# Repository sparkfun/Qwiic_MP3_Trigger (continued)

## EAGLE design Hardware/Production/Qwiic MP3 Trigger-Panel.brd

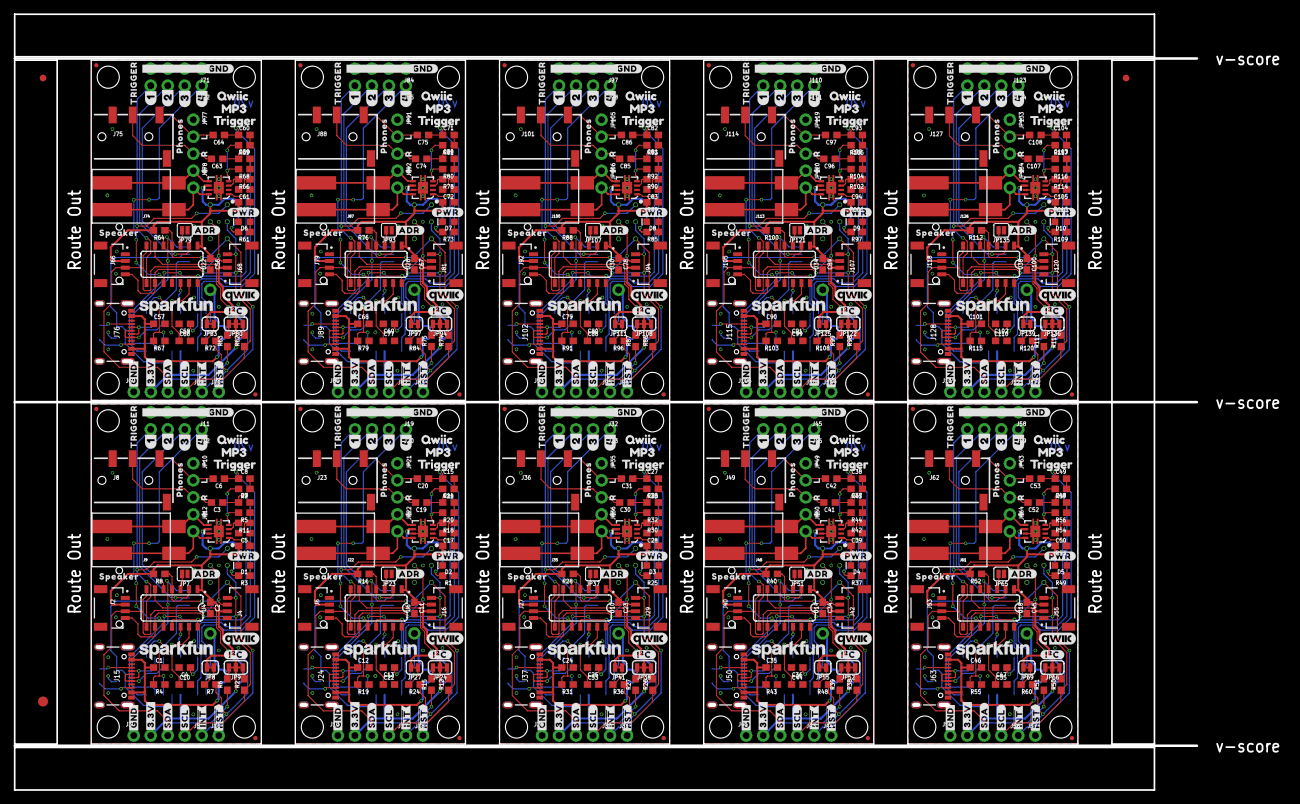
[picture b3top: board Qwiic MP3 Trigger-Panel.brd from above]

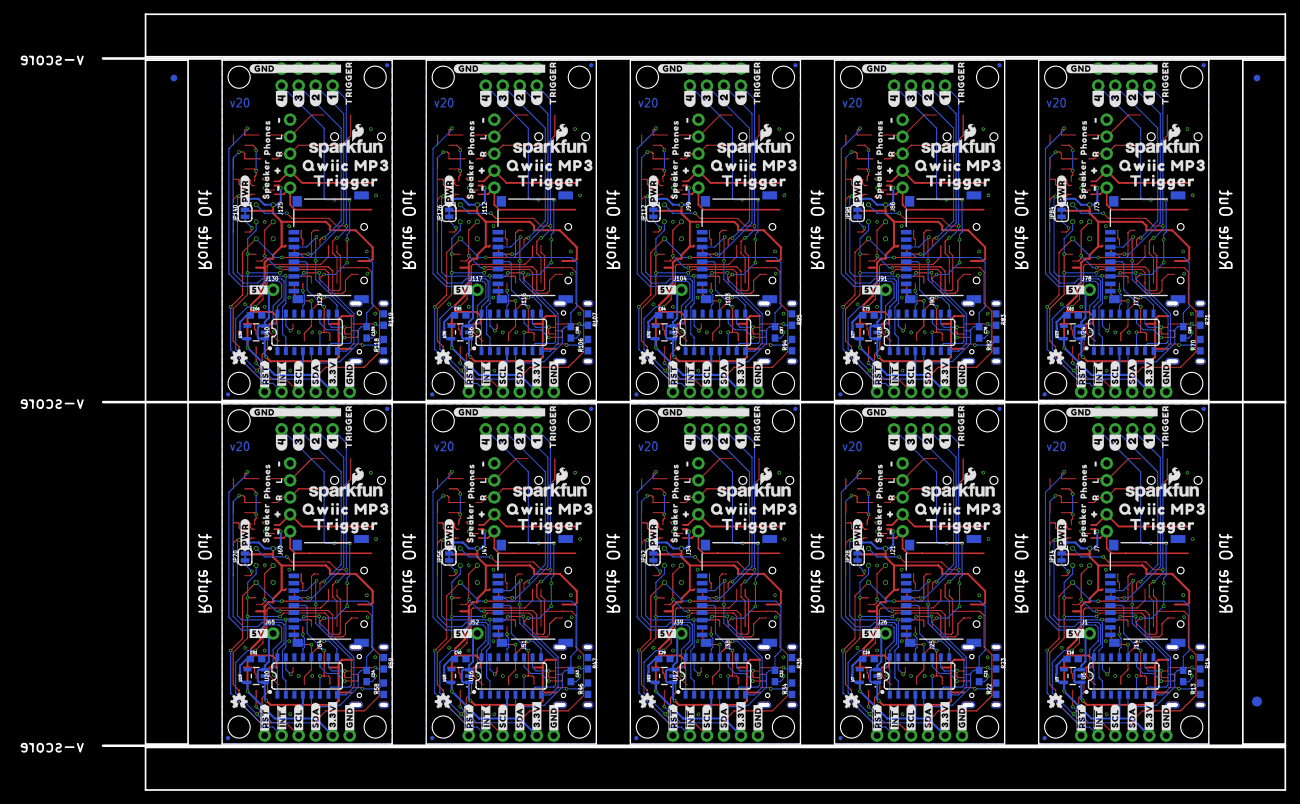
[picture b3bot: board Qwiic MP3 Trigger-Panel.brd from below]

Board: 2 copper layers, 176.5 x 115.8 mm, 1076 parts (373 on the bottom side), 410 nets.

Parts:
C1, C9, C12, C16, C18, C21, C24, C29, C32, C35, C40, C43, C46, C51, C54, C57, C62, C65, C68, C73, C76, C79, C84, C87, C90, C95, C98, C101, C106, C109: 1.0uF; 0603
C2, C11, C23, C34, C45, C56, C67, C78, C89, C100: 0.1uF; 0603
C3, C6, C19, C20, C30, C31, C41, C42, C52, C53, C63, C64, C74, C75, C85, C86, C96, C97, C107, C108: 0.22uF; 0603
C4, C10, C13, C22, C25, C33, C36, C44, C47, C55, C58, C66, C69, C77, C80, C88, C91, C99, C102, C110: 2.2uF; 0603
C5, C17, C28, C39, C50, C61, C72, C83, C94, C105: 22nF; 0603
C7, C8, C14, C15, C26, C27, C37, C38, C48, C49, C59, C60, C70, C71, C81, C82, C92, C93, C103, C104: 10nF; 0603
D1, D2, D3, D4, D5, D6, D7, D8, D9, D10: RED; LED-0603
E$1, E$2, E$3, E$4: FIDUCIAL-1X2
E$5, E$6: FIDUCIAL-1.5X3
J1, J5, J10, J17, J18, J26, J30, J31, J39, J43, J44, J52, J56, J57, J65, J69, J70, J78, J82, J83, J91, J95, J96, J104, J108, J109, J117, J121, J122, J130: 1X01_NO_SILK
J2, J4, J6, J16, J27, J29, J40, J42, J53, J55, J66, J68, J79, J81, J92, J94, J105, J107, J118, J120: QWIIC_RIGHT_ANGLE; JST04_1MM_RA
J3, J13, J28, J41, J54, J67, J80, J93, J106, J119: PTH; 1X04_NO_SILK
J7, J21, J34, J47, J60, J73, J86, J99, J112, J125: ISP; 2X3_TEST_POINTS
J8, J23, J36, J49, J62, J75, J88, J101, J114, J127: 3.5mm Audio; AUDIO_JACK_3.5MM_TRRS_SMD_RA
J9, J22, J35, J48, J61, J74, J87, J100, J113, J126: Poke-Home; 1X02_POKEHOME
J11, J12, J19, J20, J32, J33, J45, J46, J58, J59, J71, J72, J84, J85, J97, J98, J110, J111, J123, J124: 1X04_NO_SILK
J14, J25, J38, J51, J64, J77, J90, J103, J116, J129: MICRO-SD; MICROSD-EXTERNALPIN
J15, J24, J37, J50, J63, J76, J89, J102, J115, J128: USB-C-16P-2LAYER-PADS
JP1, JP2, JP5, JP6, JP17, JP18, JP19, JP20, JP31, JP32, JP33, JP34, JP45, JP46, JP47, JP48, JP59, JP60, JP61, JP62, JP73, JP74, JP75, JP76, JP87, JP88, JP89, JP90, JP101, JP102, JP103, JP104, JP115, JP116, JP117, JP118, JP129, JP130, JP131, JP132: FIDUCIALUFIDUCIAL; MICRO-FIDUCIAL
JP3, JP4, JP11, JP13, JP15, JP16, JP25, JP26, JP29, JP30, JP39, JP40, JP43, JP44, JP53, JP54, JP57, JP58, JP67, JP68, JP71, JP72, JP81, JP82, JP85, JP86, JP95, JP96, JP99, JP100, JP109, JP110, JP113, JP114, JP123, JP124, JP127, JP128, JP137, JP138: STAND-OFF
JP7, JP23, JP37, JP51, JP65, JP79, JP93, JP107, JP121, JP135: ADR; SMT-JUMPER_2_NO_SILK
JP8, JP27, JP41, JP55, JP69, JP83, JP97, JP111, JP125, JP139: INT; SMT-JUMPER_2_NC_TRACE_SILK
JP9, JP24, JP38, JP52, JP66, JP80, JP94, JP108, JP122, JP136: JUMPER-SMT_3_2-NC_TRACE_SILK; SMT-JUMPER_3_2-NC_TRACE_SILK
JP10, JP21, JP35, JP49, JP63, JP77, JP91, JP105, JP119, JP133: PTH; 1X03_NO_SILK
JP12, JP22, JP36, JP50, JP64, JP78, JP92, JP106, JP120, JP134: PTH; 1X02_NO_SILK
JP14, JP28, JP42, JP56, JP70, JP84, JP98, JP112, JP126, JP140: JUMPER-SMT_2_NC_TRACE_SILK; SMT-JUMPER_2_NC_TRACE_SILK
LOGO1, LOGO5, LOGO9, LOGO13, LOGO17, LOGO21, LOGO25, LOGO29, LOGO33, LOGO37: OSHW-LOGOMINI; OSHW-LOGO-MINI
LOGO2, LOGO6, LOGO10, LOGO14, LOGO18, LOGO22, LOGO26, LOGO30, LOGO34, LOGO38: SFE_LOGO_NAME.1_INCH; SFE_LOGO_NAME_.1
LOGO3, LOGO7, LOGO11, LOGO15, LOGO19, LOGO23, LOGO27, LOGO31, LOGO35, LOGO39: SFE_LOGO_NAME_FLAME.1_INCH; SFE_LOGO_NAME_FLAME_.1
LOGO4, LOGO8, LOGO12, LOGO16, LOGO20, LOGO24, LOGO28, LOGO32, LOGO36, LOGO40: QWIIC_LOGO_CONNECTOR; QWIIC_5.5MM
R1, R3, R25, R37, R49, R61, R73, R85, R97, R109: 1k; 0603
R2, R4, R6, R12, R15, R19, R26, R27, R31, R38, R39, R43, R50, R51, R55, R62, R63, R67, R74, R75, R79, R86, R87, R91, R98, R99, R103, R110, R111, R115: 2.2k; 0603
R5, R9, R20, R21, R32, R33, R44, R45, R56, R57, R68, R69, R80, R81, R92, R93, R104, R105, R116, R117: 100k; 0603
R7, R8, R10, R16, R17, R24, R28, R29, R36, R40, R41, R48, R52, R53, R60, R64, R65, R72, R76, R77, R84, R88, R89, R96, R100, R101, R108, R112, R113, R120: 10k; 0603
R11, R18, R30, R42, R54, R66, R78, R90, R102, R114: 47k; 0603
R13, R14, R22, R23, R34, R35, R46, R47, R58, R59, R70, R71, R82, R83, R94, R95, R106, R107, R118, R119: 5.1k; 0603
U1, U2, U9, U13, U17, U21, U25, U29, U33, U37: TPA2005D1; QFN-8_PAD
U3, U7, U11, U15, U19, U23, U27, U31, U35, U39: AP2112-3.3V; SOT23-5
U4, U6, U10, U14, U18, U22, U26, U30, U34, U38: ATTINY84-ARDUINO; SO14
U5, U8, U12, U16, U20, U24, U28, U32, U36, U40: MY1690X-16S; SO16
U$1, U$4, U$97, U$145, U$193, U$241, U$289, U$337, U$385, U$433: MP31
U$2, U$27, U$30, U$47, U$109, U$110, U$157, U$158, U$205, U$206, U$253, U$254, U$301, U$302, U$349, U$350, U$397, U$398, U$445, U$446: TRIGGER0
U$3, U$96, U$144, U$192, U$240, U$288, U$336, U$384, U$432, U$480: #5V#0
U$5, U$23, U$98, U$146, U$194, U$242, U$290, U$338, U$386, U$434: QWIIC0
U$6, U$50, U$99, U$147, U$195, U$243, U$291, U$339, U$387, U$435: TRIGGER2
U$7, U$32, U$48, U$79, U$100, U$127, U$148, U$175, U$196, U$223, U$244, U$271, U$292, U$319, U$340, U$367, U$388, U$415, U$436, U$463: PHONES0
U$8, U$18, U$40, U$82, U$101, U$130, U$149, U$178, U$197, U$226, U$245, U$274, U$293, U$322, U$341, U$370, U$389, U$418, U$437, U$466: SPEAKER0
U$9, U$11, U$14, U$51, U$102, U$103, U$150, U$151, U$198, U$199, U$246, U$247, U$294, U$295, U$342, U$343, U$390, U$391, U$438, U$439: #0
U$10, U$38, U$69, U$70, U$117, U$118, U$165, U$166, U$213, U$214, U$261, U$262, U$309, U$310, U$357, U$358, U$405, U$406, U$453, U$454: #1#3
U$12, U$13, U$16, U$28, U$104, U$105, U$152, U$153, U$200, U$201, U$248, U$249, U$296, U$297, U$344, U$345, U$392, U$393, U$440, U$441: #1
U$15, U$24, U$26, U$80, U$108, U$128, U$156, U$176, U$204, U$224, U$252, U$272, U$300, U$320, U$348, U$368, U$396, U$416, U$444, U$464: #PWR#0
U$17, U$81, U$129, U$177, U$225, U$273, U$321, U$369, U$417, U$465: #ADR#0
U$19, U$31, U$77, U$78, U$125, U$126, U$173, U$174, U$221, U$222, U$269, U$270, U$317, U$318, U$365, U$366, U$413, U$414, U$461, U$462: #GND#0
U$20, U$83, U$131, U$179, U$227, U$275, U$323, U$371, U$419, U$467: #I�C#0
U$21, U$25, U$106, U$154, U$202, U$250, U$298, U$346, U$394, U$442: QWIIC_MP30
U$22, U$52, U$107, U$155, U$203, U$251, U$299, U$347, U$395, U$443: TRIGGER1
U$29, U$45, U$63, U$64, U$111, U$112, U$159, U$160, U$207, U$208, U$255, U$256, U$303, U$304, U$351, U$352, U$399, U$400, U$447, U$448: L1
U$33, U$34, U$84, U$85, U$132, U$133, U$180, U$181, U$228, U$229, U$276, U$277, U$324, U$325, U$372, U$373, U$420, U$421, U$468, U$469: ##INT##4
U$35, U$36, U$86, U$87, U$134, U$135, U$182, U$183, U$230, U$231, U$278, U$279, U$326, U$327, U$374, U$375, U$422, U$423, U$470, U$471: ##RST##5
U$37, U$39, U$65, U$66, U$113, U$114, U$161, U$162, U$209, U$210, U$257, U$258, U$305, U$306, U$353, U$354, U$401, U$402, U$449, U$450: R0
U$41, U$43, U$67, U$68, U$115, U$116, U$163, U$164, U$211, U$212, U$259, U$260, U$307, U$308, U$355, U$356, U$403, U$404, U$451, U$452: #2
U$42, U$44, U$88, U$89, U$136, U$137, U$184, U$185, U$232, U$233, U$280, U$281, U$328, U$329, U$376, U$377, U$424, U$425, U$472, U$473: #3#3V#0
U$46, U$58, U$90, U$91, U$138, U$139, U$186, U$187, U$234, U$235, U$282, U$283, U$330, U$331, U$378, U$379, U$426, U$427, U$474, U$475: #GND#1
U$49, U$53, U$71, U$72, U$119, U$120, U$167, U$168, U$215, U$216, U$263, U$264, U$311, U$312, U$359, U$360, U$407, U$408, U$455, U$456: #2#2
U$54, U$55, U$73, U$74, U$121, U$122, U$169, U$170, U$217, U$218, U$265, U$266, U$313, U$314, U$361, U$362, U$409, U$410, U$457, U$458: #3#1
U$56, U$57, U$75, U$76, U$123, U$124, U$171, U$172, U$219, U$220, U$267, U$268, U$315, U$316, U$363, U$364, U$411, U$412, U$459, U$460: #4#0
U$59, U$60, U$92, U$93, U$140, U$141, U$188, U$189, U$236, U$237, U$284, U$285, U$332, U$333, U$380, U$381, U$428, U$429, U$476, U$477: #SCL#3
U$61, U$62, U$94, U$95, U$142, U$143, U$190, U$191, U$238, U$239, U$286, U$287, U$334, U$335, U$382, U$383, U$430, U$431, U$478, U$479: #SDA#2

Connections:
3.3V: C2.1, C16.1, J2.2, J3.2, J4.2, J7.2, JP8.2, JP9.2, JP14.2, R8.2, R10.2, U1.6, U3.5, U4.1, U5.4
3.3V1: C11.1, C18.1, J6.2, J13.2, J16.2, J21.2, JP24.2, JP27.2, JP28.2, R16.2, R17.2, U2.6, U6.1, U7.5, U8.4
3.3V2: C23.1, C29.1, J27.2, J28.2, J29.2, J34.2, JP38.2, JP41.2, JP42.2, R28.2, R29.2, U9.6, U10.1, U11.5, U12.4
3.3V3: C34.1, C40.1, J40.2, J41.2, J42.2, J47.2, JP52.2, JP55.2, JP56.2, R40.2, R41.2, U13.6, U14.1, U15.5, U16.4
3.3V4: C45.1, C51.1, J53.2, J54.2, J55.2, J60.2, JP66.2, JP69.2, JP70.2, R52.2, R53.2, U17.6, U18.1, U19.5, U20.4
3.3V5: C56.1, C62.1, J66.2, J67.2, J68.2, J73.2, JP80.2, JP83.2, JP84.2, R64.2, R65.2, U21.6, U22.1, U23.5, U24.4
3.3V6: C67.1, C73.1, J79.2, J80.2, J81.2, J86.2, JP94.2, JP97.2, JP98.2, R76.2, R77.2, U25.6, U26.1, U27.5, U28.4
3.3V7: C78.1, C84.1, J92.2, J93.2, J94.2, J99.2, JP108.2, JP111.2, JP112.2, R88.2, R89.2, U29.6, U30.1, U31.5, U32.4
3.3V8: C89.1, C95.1, J105.2, J106.2, J107.2, J112.2, JP122.2, JP125.2, JP126.2, R100.2, R101.2, U33.6, U34.1, U35.5, U36.4
3.3V9: C100.1, C106.1, J118.2, J119.2, J120.2, J125.2, JP136.2, JP139.2, JP140.2, R112.2, R113.2, U37.6, U38.1, U39.5, U40.4
5V: C1.1, J1.1, J15.VBUS1, J15.VBUS2, U3.1, U3.3
5V1: C12.1, J24.VBUS1, J24.VBUS2, J26.1, U7.1, U7.3
5V2: C24.1, J37.VBUS1, J37.VBUS2, J39.1, U11.1, U11.3
5V3: C35.1, J50.VBUS1, J50.VBUS2, J52.1, U15.1, U15.3
5V4: C46.1, J63.VBUS1, J63.VBUS2, J65.1, U19.1, U19.3
5V5: C57.1, J76.VBUS1, J76.VBUS2, J78.1, U23.1, U23.3
5V6: C68.1, J89.VBUS1, J89.VBUS2, J91.1, U27.1, U27.3
5V7: C79.1, J102.VBUS1, J102.VBUS2, J104.1, U31.1, U31.3
5V8: C90.1, J115.VBUS1, J115.VBUS2, J117.1, U35.1, U35.3
5V9: C101.1, J128.VBUS1, J128.VBUS2, J130.1, U39.1, U39.3
!INT: J5.1, R7.1, U4.6
!INT1: J17.1, R24.1, U6.6
!INT2: J30.1, R36.1, U10.6
!INT3: J43.1, R48.1, U14.6
!INT4: J56.1, R60.1, U18.6
!INT5: J69.1, R72.1, U22.6
!INT6: J82.1, R84.1, U26.6
!INT7: J95.1, R96.1, U30.6
!INT8: J108.1, R108.1, U34.6
!INT9: J121.1, R120.1, U38.6
!RST: J7.5, J10.1, R8.1, U4.4
!RST1: J18.1, J21.5, R16.1, U6.4
!RST2: J31.1, J34.5, R28.1, U10.4
!RST3: J44.1, J47.5, R40.1, U14.4
!RST4: J57.1, J60.5, R52.1, U18.4
!RST5: J70.1, J73.5, R64.1, U22.4
!RST6: J83.1, J86.5, R76.1, U26.4
!RST7: J96.1, J99.5, R88.1, U30.4
!RST8: J109.1, J112.5, R100.1, U34.4
!RST9: J122.1, J125.5, R112.1, U38.4
AC-L: C3.2, J8.RING1, JP10.3
AC-L1: C19.2, J23.RING1, JP21.3
AC-L2: C30.2, J36.RING1, JP35.3
AC-L3: C41.2, J49.RING1, JP49.3
AC-L4: C52.2, J62.RING1, JP63.3
AC-L5: C63.2, J75.RING1, JP77.3
AC-L6: C74.2, J88.RING1, JP91.3
AC-L7: C85.2, J101.RING1, JP105.3
AC-L8: C96.2, J114.RING1, JP119.3
AC-L9: C107.2, J127.RING1, JP133.3
AC-R: C6.2, J8.TIP, JP10.2
AC-R1: C20.2, J23.TIP, JP21.2
AC-R2: C31.2, J36.TIP, JP35.2
AC-R3: C42.2, J49.TIP, JP49.2
AC-R4: C53.2, J62.TIP, JP63.2
AC-R5: C64.2, J75.TIP, JP77.2
AC-R6: C75.2, J88.TIP, JP91.2
AC-R7: C86.2, J101.TIP, JP105.2
AC-R8: C97.2, J114.TIP, JP119.2
AC-R9: C108.2, J127.TIP, JP133.2
ADR: JP7.2, U4.3
ADR1: JP23.2, U6.3
ADR2: JP37.2, U10.3
ADR3: JP51.2, U14.3
ADR4: JP65.2, U18.3
ADR5: JP79.2, U22.3
ADR6: JP93.2, U26.3
ADR7: JP107.2, U30.3
ADR8: JP121.2, U34.3
ADR9: JP135.2, U38.3
D+: J15.A6, J15.B6, U5.11
D+1: J24.A6, J24.B6, U8.11
D+2: J37.A6, J37.B6, U12.11
D+3: J50.A6, J50.B6, U16.11
D+4: J63.A6, J63.B6, U20.11
D+5: J76.A6, J76.B6, U24.11
D+6: J89.A6, J89.B6, U28.11
D+7: J102.A6, J102.B6, U32.11
D+8: J115.A6, J115.B6, U36.11
D+9: J128.A6, J128.B6, U40.11
D-: J15.A7, J15.B7, U5.10
D-1: J24.A7, J24.B7, U8.10
D-2: J37.A7, J37.B7, U12.10
D-3: J50.A7, J50.B7, U16.10
D-4: J63.A7, J63.B7, U20.10
D-5: J76.A7, J76.B7, U24.10
D-6: J89.A7, J89.B7, U28.10
D-7: J102.A7, J102.B7, U32.10
D-8: J115.A7, J115.B7, U36.10
D-9: J128.A7, J128.B7, U40.10
GND: C1.2, C2.2, C4.2, C5.1, C9.2, C10.2, C16.2, D1.C, J2.1, J3.1, J4.1, J7.6, J8.EARTH, J8.RING2, J11.1, J11.2, J11.3, J11.4, J14.6, J14.10, J14.11, J14.12, J14.13, J15.GND, J15.GND2, J15.SHLD1, J15.SHLD2, J15.SHLD3, J15.SHLD4, JP7.1, JP10.1, R4.1, R13.1, R14.1, U1.7, U1.9, U1.10, U1.11, U1.12, U1.13, U3.2, U4.14, U5.3, U5.14
GND1: C11.2, C12.2, C13.2, C17.1, C18.2, C21.2, C22.2, D2.C, J6.1, J13.1, J16.1, J19.1, J19.2, J19.3, J19.4, J21.6, J23.EARTH, J23.RING2, J24.GND, J24.GND2, J24.SHLD1, J24.SHLD2, J24.SHLD3, J24.SHLD4, J25.6, J25.10, J25.11, J25.12, J25.13, JP21.1, JP23.1, R19.1, R22.1, R23.1, U2.7, U2.9, U2.10, U2.11, U2.12, U2.13, U6.14, U7.2, U8.3, U8.14
GND2: C23.2, C24.2, C25.2, C28.1, C29.2, C32.2, C33.2, D3.C, J27.1, J28.1, J29.1, J32.1, J32.2, J32.3, J32.4, J34.6, J36.EARTH, J36.RING2, J37.GND, J37.GND2, J37.SHLD1, J37.SHLD2, J37.SHLD3, J37.SHLD4, J38.6, J38.10, J38.11, J38.12, J38.13, JP35.1, JP37.1, R31.1, R34.1, R35.1, U9.7, U9.9, U9.10, U9.11, U9.12, U9.13, U10.14, U11.2, U12.3, U12.14
GND3: C34.2, C35.2, C36.2, C39.1, C40.2, C43.2, C44.2, D4.C, J40.1, J41.1, J42.1, J45.1, J45.2, J45.3, J45.4, J47.6, J49.EARTH, J49.RING2, J50.GND, J50.GND2, J50.SHLD1, J50.SHLD2, J50.SHLD3, J50.SHLD4, J51.6, J51.10, J51.11, J51.12, J51.13, JP49.1, JP51.1, R43.1, R46.1, R47.1, U13.7, U13.9, U13.10, U13.11, U13.12, U13.13, U14.14, U15.2, U16.3, U16.14
GND4: C45.2, C46.2, C47.2, C50.1, C51.2, C54.2, C55.2, D5.C, J53.1, J54.1, J55.1, J58.1, J58.2, J58.3, J58.4, J60.6, J62.EARTH, J62.RING2, J63.GND, J63.GND2, J63.SHLD1, J63.SHLD2, J63.SHLD3, J63.SHLD4, J64.6, J64.10, J64.11, J64.12, J64.13, JP63.1, JP65.1, R55.1, R58.1, R59.1, U17.7, U17.9, U17.10, U17.11, U17.12, U17.13, U18.14, U19.2, U20.3, U20.14
GND5: C56.2, C57.2, C58.2, C61.1, C62.2, C65.2, C66.2, D6.C, J66.1, J67.1, J68.1, J71.1, J71.2, J71.3, J71.4, J73.6, J75.EARTH, J75.RING2, J76.GND, J76.GND2, J76.SHLD1, J76.SHLD2, J76.SHLD3, J76.SHLD4, J77.6, J77.10, J77.11, J77.12, J77.13, JP77.1, JP79.1, R67.1, R70.1, R71.1, U21.7, U21.9, U21.10, U21.11, U21.12, U21.13, U22.14, U23.2, U24.3, U24.14
GND6: C67.2, C68.2, C69.2, C72.1, C73.2, C76.2, C77.2, D7.C, J79.1, J80.1, J81.1, J84.1, J84.2, J84.3, J84.4, J86.6, J88.EARTH, J88.RING2, J89.GND, J89.GND2, J89.SHLD1, J89.SHLD2, J89.SHLD3, J89.SHLD4, J90.6, J90.10, J90.11, J90.12, J90.13, JP91.1, JP93.1, R79.1, R82.1, R83.1, U25.7, U25.9, U25.10, U25.11, U25.12, U25.13, U26.14, U27.2, U28.3, U28.14
GND7: C78.2, C79.2, C80.2, C83.1, C84.2, C87.2, C88.2, D8.C, J92.1, J93.1, J94.1, J97.1, J97.2, J97.3, J97.4, J99.6, J101.EARTH, J101.RING2, J102.GND, J102.GND2, J102.SHLD1, J102.SHLD2, J102.SHLD3, J102.SHLD4, J103.6, J103.10, J103.11, J103.12, J103.13, JP105.1, JP107.1, R91.1, R94.1, R95.1, U29.7, U29.9, U29.10, U29.11, U29.12, U29.13, U30.14, U31.2, U32.3, U32.14
GND8: C89.2, C90.2, C91.2, C94.1, C95.2, C98.2, C99.2, D9.C, J105.1, J106.1, J107.1, J110.1, J110.2, J110.3, J110.4, J112.6, J114.EARTH, J114.RING2, J115.GND, J115.GND2, J115.SHLD1, J115.SHLD2, J115.SHLD3, J115.SHLD4, J116.6, J116.10, J116.11, J116.12, J116.13, JP119.1, JP121.1, R103.1, R106.1, R107.1, U33.7, U33.9, U33.10, U33.11, U33.12, U33.13, U34.14, U35.2, U36.3, U36.14
GND9: C100.2, C101.2, C102.2, C105.1, C106.2, C109.2, C110.2, D10.C, J118.1, J119.1, J120.1, J123.1, J123.2, J123.3, J123.4, J125.6, J127.EARTH, J127.RING2, J128.GND, J128.GND2, J128.SHLD1, J128.SHLD2, J128.SHLD3, J128.SHLD4, J129.6, J129.10, J129.11, J129.12, J129.13, JP133.1, JP135.1, R115.1, R118.1, R119.1, U37.7, U37.9, U37.10, U37.11, U37.12, U37.13, U38.14, U39.2, U40.3, U40.14
IN+AMP: R11.2, U1.3
IN+AMP1: R18.2, U2.3
IN+AMP2: R30.2, U9.3
IN+AMP3: R42.2, U13.3
IN+AMP4: R54.2, U17.3
IN+AMP5: R66.2, U21.3
IN+AMP6: R78.2, U25.3
IN+AMP7: R90.2, U29.3
IN+AMP8: R102.2, U33.3
IN+AMP9: R114.2, U37.3
IN-AMP: R5.2, R9.2, U1.4
IN-AMP1: R20.2, R21.2, U2.4
IN-AMP2: R32.2, R33.2, U9.4
IN-AMP3: R44.2, R45.2, U13.4
IN-AMP4: R56.2, R57.2, U17.4
IN-AMP5: R68.2, R69.2, U21.4
IN-AMP6: R80.2, R81.2, U25.4
IN-AMP7: R92.2, R93.2, U29.4
IN-AMP8: R104.2, R105.2, U33.4
IN-AMP9: R116.2, R117.2, U37.4
MP3-RXI: U4.13, U5.12
MP3-RXI1: U6.13, U8.12
MP3-RXI2: U10.13, U12.12
MP3-RXI3: U14.13, U16.12
MP3-RXI4: U18.13, U20.12
MP3-RXI5: U22.13, U24.12
MP3-RXI6: U26.13, U28.12
MP3-RXI7: U30.13, U32.12
MP3-RXI8: U34.13, U36.12
MP3-RXI9: U38.13, U40.12
MP3-TXO: U4.12, U5.13
MP3-TXO1: U6.12, U8.13
MP3-TXO2: U10.12, U12.13
MP3-TXO3: U14.12, U16.13
MP3-TXO4: U18.12, U20.13
MP3-TXO5: U22.12, U24.13
MP3-TXO6: U26.12, U28.13
MP3-TXO7: U30.12, U32.13
MP3-TXO8: U34.12, U36.13
MP3-TXO9: U38.12, U40.13
unnamed: J15.B5, R13.2
unnamed: J15.A5, R14.2
unnamed: D1.A, R3.1
unnamed: JP8.1, R7.2
unnamed: C8.2, R9.1
unnamed: JP14.1, R3.2
unnamed: C4.1, U5.15
unnamed: C5.2, R11.1
unnamed: C7.2, R5.1
unnamed: C10.1, U5.9
unnamed: D2.A, R1.1
unnamed: C17.2, R18.1
unnamed: C14.2, R20.1
unnamed: C15.2, R21.1
unnamed: J24.B5, R22.2
unnamed: J24.A5, R23.2
unnamed: JP27.1, R24.2
unnamed: JP28.1, R1.2
unnamed: C13.1, U8.15
unnamed: C22.1, U8.9
unnamed: D3.A, R25.1
unnamed: C28.2, R30.1
unnamed: C26.2, R32.1
unnamed: C27.2, R33.1
unnamed: J37.B5, R34.2
unnamed: J37.A5, R35.2
unnamed: JP41.1, R36.2
unnamed: JP42.1, R25.2
unnamed: C25.1, U12.15
unnamed: C33.1, U12.9
unnamed: D4.A, R37.1
unnamed: C39.2, R42.1
unnamed: C37.2, R44.1
unnamed: C38.2, R45.1
unnamed: J50.B5, R46.2
unnamed: J50.A5, R47.2
unnamed: JP55.1, R48.2
unnamed: JP56.1, R37.2
unnamed: C36.1, U16.15
unnamed: C44.1, U16.9
unnamed: D5.A, R49.1
unnamed: C50.2, R54.1
unnamed: C48.2, R56.1
unnamed: C49.2, R57.1
unnamed: J63.B5, R58.2
unnamed: J63.A5, R59.2
unnamed: JP69.1, R60.2
unnamed: JP70.1, R49.2
unnamed: C47.1, U20.15
unnamed: C55.1, U20.9
unnamed: D6.A, R61.1
unnamed: C61.2, R66.1
unnamed: C59.2, R68.1
unnamed: C60.2, R69.1
unnamed: J76.B5, R70.2
unnamed: J76.A5, R71.2
unnamed: JP83.1, R72.2
unnamed: JP84.1, R61.2
unnamed: C58.1, U24.15
unnamed: C66.1, U24.9
unnamed: D7.A, R73.1
unnamed: C72.2, R78.1
unnamed: C70.2, R80.1
unnamed: C71.2, R81.1
unnamed: J89.B5, R82.2
unnamed: J89.A5, R83.2
unnamed: JP97.1, R84.2
unnamed: JP98.1, R73.2
unnamed: C69.1, U28.15
unnamed: C77.1, U28.9
unnamed: D8.A, R85.1
unnamed: C83.2, R90.1
unnamed: C81.2, R92.1
unnamed: C82.2, R93.1
unnamed: J102.B5, R94.2
unnamed: J102.A5, R95.2
unnamed: JP111.1, R96.2
unnamed: JP112.1, R85.2
unnamed: C80.1, U32.15
unnamed: C88.1, U32.9
unnamed: D9.A, R97.1
unnamed: C94.2, R102.1
unnamed: C92.2, R104.1
unnamed: C93.2, R105.1
unnamed: J115.B5, R106.2
unnamed: J115.A5, R107.2
unnamed: JP125.1, R108.2
unnamed: JP126.1, R97.2
unnamed: C91.1, U36.15
unnamed: C99.1, U36.9
unnamed: D10.A, R109.1
unnamed: C105.2, R114.1
unnamed: C103.2, R116.1
unnamed: C104.2, R117.1
unnamed: J128.B5, R118.2
unnamed: J128.A5, R119.2
unnamed: JP139.1, R120.2
unnamed: JP140.1, R109.2
unnamed: C102.1, U40.15
unnamed: C110.1, U40.9
OUT+: J9.P1, J9.P3, JP12.1, U1.5
OUT+1: J22.P1, J22.P3, JP22.1, U2.5
OUT+2: J35.P1, J35.P3, JP36.1, U9.5
OUT+3: J48.P1, J48.P3, JP50.1, U13.5
OUT+4: J61.P1, J61.P3, JP64.1, U17.5
OUT+5: J74.P1, J74.P3, JP78.1, U21.5
OUT+6: J87.P1, J87.P3, JP92.1, U25.5
OUT+7: J100.P1, J100.P3, JP106.1, U29.5
OUT+8: J113.P1, J113.P3, JP120.1, U33.5
OUT+9: J126.P1, J126.P3, JP134.1, U37.5
OUT-: J9.P2, J9.P4, JP12.2, U1.8
OUT-1: J22.P2, J22.P4, JP22.2, U2.8
OUT-2: J35.P2, J35.P4, JP36.2, U9.8
OUT-3: J48.P2, J48.P4, JP50.2, U13.8
OUT-4: J61.P2, J61.P4, JP64.2, U17.8
OUT-5: J74.P2, J74.P4, JP78.2, U21.8
OUT-6: J87.P2, J87.P4, JP92.2, U25.8
OUT-7: J100.P2, J100.P4, JP106.2, U29.8
OUT-8: J113.P2, J113.P4, JP120.2, U33.8
OUT-9: J126.P2, J126.P4, JP134.2, U37.8
PLAYING: R10.1, U1.1, U4.11, U5.2
PLAYING1: R17.1, U2.1, U6.11, U8.2
PLAYING2: R29.1, U9.1, U10.11, U12.2
PLAYING3: R41.1, U13.1, U14.11, U16.2
PLAYING4: R53.1, U17.1, U18.11, U20.2
PLAYING5: R65.1, U21.1, U22.11, U24.2
PLAYING6: R77.1, U25.1, U26.11, U28.2
PLAYING7: R89.1, U29.1, U30.11, U32.2
PLAYING8: R101.1, U33.1, U34.11, U36.2
PLAYING9: R113.1, U37.1, U38.11, U40.2
SCL: J2.4, J3.4, J4.4, J7.3, R2.1, U4.9
SCL1: J6.4, J13.4, J16.4, J21.3, R12.1, U6.9
SCL2: J27.4, J28.4, J29.4, J34.3, R26.1, U10.9
SCL3: J40.4, J41.4, J42.4, J47.3, R38.1, U14.9
SCL4: J53.4, J54.4, J55.4, J60.3, R50.1, U18.9
SCL5: J66.4, J67.4, J68.4, J73.3, R62.1, U22.9
SCL6: J79.4, J80.4, J81.4, J86.3, R74.1, U26.9
SCL7: J92.4, J93.4, J94.4, J99.3, R86.1, U30.9
SCL8: J105.4, J106.4, J107.4, J112.3, R98.1, U34.9
SCL9: J118.4, J119.4, J120.4, J125.3, R110.1, U38.9
SCL_PU1: JP9.1, R2.2
SCL_PU2: JP24.1, R12.2
SCL_PU3: JP38.1, R26.2
SCL_PU4: JP52.1, R38.2
SCL_PU5: JP66.1, R50.2
SCL_PU6: JP80.1, R62.2
SCL_PU7: JP94.1, R74.2
SCL_PU8: JP108.1, R86.2
SCL_PU9: JP122.1, R98.2
SCL_PU10: JP136.1, R110.2
SDA: J2.3, J3.3, J4.3, J7.4, R6.1, U4.7
SDA1: J6.3, J13.3, J16.3, J21.4, R15.1, U6.7
SDA2: J27.3, J28.3, J29.3, J34.4, R27.1, U10.7
SDA3: J40.3, J41.3, J42.3, J47.4, R39.1, U14.7
SDA4: J53.3, J54.3, J55.3, J60.4, R51.1, U18.7
SDA5: J66.3, J67.3, J68.3, J73.4, R63.1, U22.7
SDA6: J79.3, J80.3, J81.3, J86.4, R75.1, U26.7
SDA7: J92.3, J93.3, J94.3, J99.4, R87.1, U30.7
SDA8: J105.3, J106.3, J107.3, J112.4, R99.1, U34.7
SDA9: J118.3, J119.3, J120.3, J125.4, R111.1, U38.7
SDA_PU1: JP9.3, R6.2
SDA_PU2: JP24.3, R15.2
SDA_PU3: JP38.3, R27.2
SDA_PU4: JP52.3, R39.2
SDA_PU5: JP66.3, R51.2
SDA_PU6: JP80.3, R63.2
SDA_PU7: JP94.3, R75.2
SDA_PU8: JP108.3, R87.2
SDA_PU9: JP122.3, R99.2
SDA_PU10: JP136.3, R111.2
SD_CLK: J14.5, R4.2, U5.6
SD_CLK1: J25.5, R19.2, U8.6
SD_CLK2: J38.5, R31.2, U12.6
SD_CLK3: J51.5, R43.2, U16.6
SD_CLK4: J64.5, R55.2, U20.6
SD_CLK5: J77.5, R67.2, U24.6
SD_CLK6: J90.5, R79.2, U28.6
SD_CLK7: J103.5, R91.2, U32.6
SD_CLK8: J116.5, R103.2, U36.6
SD_CLK9: J129.5, R115.2, U40.6
SD_CMD: J14.3, U5.7
SD_CMD1: J25.3, U8.7
SD_CMD2: J38.3, U12.7
SD_CMD3: J51.3, U16.7
SD_CMD4: J64.3, U20.7
SD_CMD5: J77.3, U24.7
SD_CMD6: J90.3, U28.7
SD_CMD7: J103.3, U32.7
SD_CMD8: J116.3, U36.7
SD_CMD9: J129.3, U40.7
SD_DAT: J14.7, U5.8
SD_DAT1: J25.7, U8.8
SD_DAT2: J38.7, U12.8
SD_DAT3: J51.7, U16.8
SD_DAT4: J64.7, U20.8
SD_DAT5: J77.7, U24.8
SD_DAT6: J90.7, U28.8
SD_DAT7: J103.7, U32.8
SD_DAT8: J116.7, U36.8
SD_DAT9: J129.7, U40.8
TRIGGER1: J7.1, J12.4, U4.8
TRIGGER2: J12.3, U4.2
TRIGGER3: J12.2, U4.5
TRIGGER4: J12.1, U4.10
TRIGGER5: J20.1, U6.10
TRIGGER6: J20.4, J21.1, U6.8
TRIGGER7: J20.3, U6.2
TRIGGER8: J20.2, U6.5
TRIGGER9: J33.1, U10.10
TRIGGER10: J33.4, J34.1, U10.8
TRIGGER11: J33.3, U10.2
TRIGGER12: J33.2, U10.5
TRIGGER13: J46.1, U14.10
TRIGGER14: J46.4, J47.1, U14.8
TRIGGER15: J46.3, U14.2
TRIGGER16: J46.2, U14.5
TRIGGER17: J59.1, U18.10
TRIGGER18: J59.4, J60.1, U18.8
TRIGGER19: J59.3, U18.2
TRIGGER20: J59.2, U18.5
TRIGGER21: J72.1, U22.10
TRIGGER22: J72.4, J73.1, U22.8
TRIGGER23: J72.3, U22.2
TRIGGER24: J72.2, U22.5
TRIGGER25: J85.1, U26.10
TRIGGER26: J85.4, J86.1, U26.8
TRIGGER27: J85.3, U26.2
TRIGGER28: J85.2, U26.5
TRIGGER29: J98.1, U30.10
TRIGGER30: J98.4, J99.1, U30.8
TRIGGER31: J98.3, U30.2
TRIGGER32: J98.2, U30.5
TRIGGER33: J111.1, U34.10
TRIGGER34: J111.4, J112.1, U34.8
TRIGGER35: J111.3, U34.2
TRIGGER36: J111.2, U34.5
TRIGGER37: J124.1, U38.10
TRIGGER38: J124.4, J125.1, U38.8
TRIGGER39: J124.3, U38.2
TRIGGER40: J124.2, U38.5
VCCIO: C9.1, J14.4, U5.5
VCCIO1: C21.1, J25.4, U8.5
VCCIO2: C32.1, J38.4, U12.5
VCCIO3: C43.1, J51.4, U16.5
VCCIO4: C54.1, J64.4, U20.5
VCCIO5: C65.1, J77.4, U24.5
VCCIO6: C76.1, J90.4, U28.5
VCCIO7: C87.1, J103.4, U32.5
VCCIO8: C98.1, J116.4, U36.5
VCCIO9: C109.1, J129.4, U40.5
VOUTL: C3.1, C7.1, U5.16
VOUTL1: C14.1, C19.1, U8.16
VOUTL2: C26.1, C30.1, U12.16
VOUTL3: C37.1, C41.1, U16.16
VOUTL4: C48.1, C52.1, U20.16
VOUTL5: C59.1, C63.1, U24.16
VOUTL6: C70.1, C74.1, U28.16
VOUTL7: C81.1, C85.1, U32.16
VOUTL8: C92.1, C96.1, U36.16
VOUTL9: C103.1, C107.1, U40.16
VOUTR: C6.1, C8.1, U5.1
VOUTR1: C15.1, C20.1, U8.1
VOUTR2: C27.1, C31.1, U12.1
VOUTR3: C38.1, C42.1, U16.1
VOUTR4: C49.1, C53.1, U20.1
VOUTR5: C60.1, C64.1, U24.1
VOUTR6: C71.1, C75.1, U28.1
VOUTR7: C82.1, C86.1, U32.1
VOUTR8: C93.1, C97.1, U36.1
VOUTR9: C104.1, C108.1, U40.1
